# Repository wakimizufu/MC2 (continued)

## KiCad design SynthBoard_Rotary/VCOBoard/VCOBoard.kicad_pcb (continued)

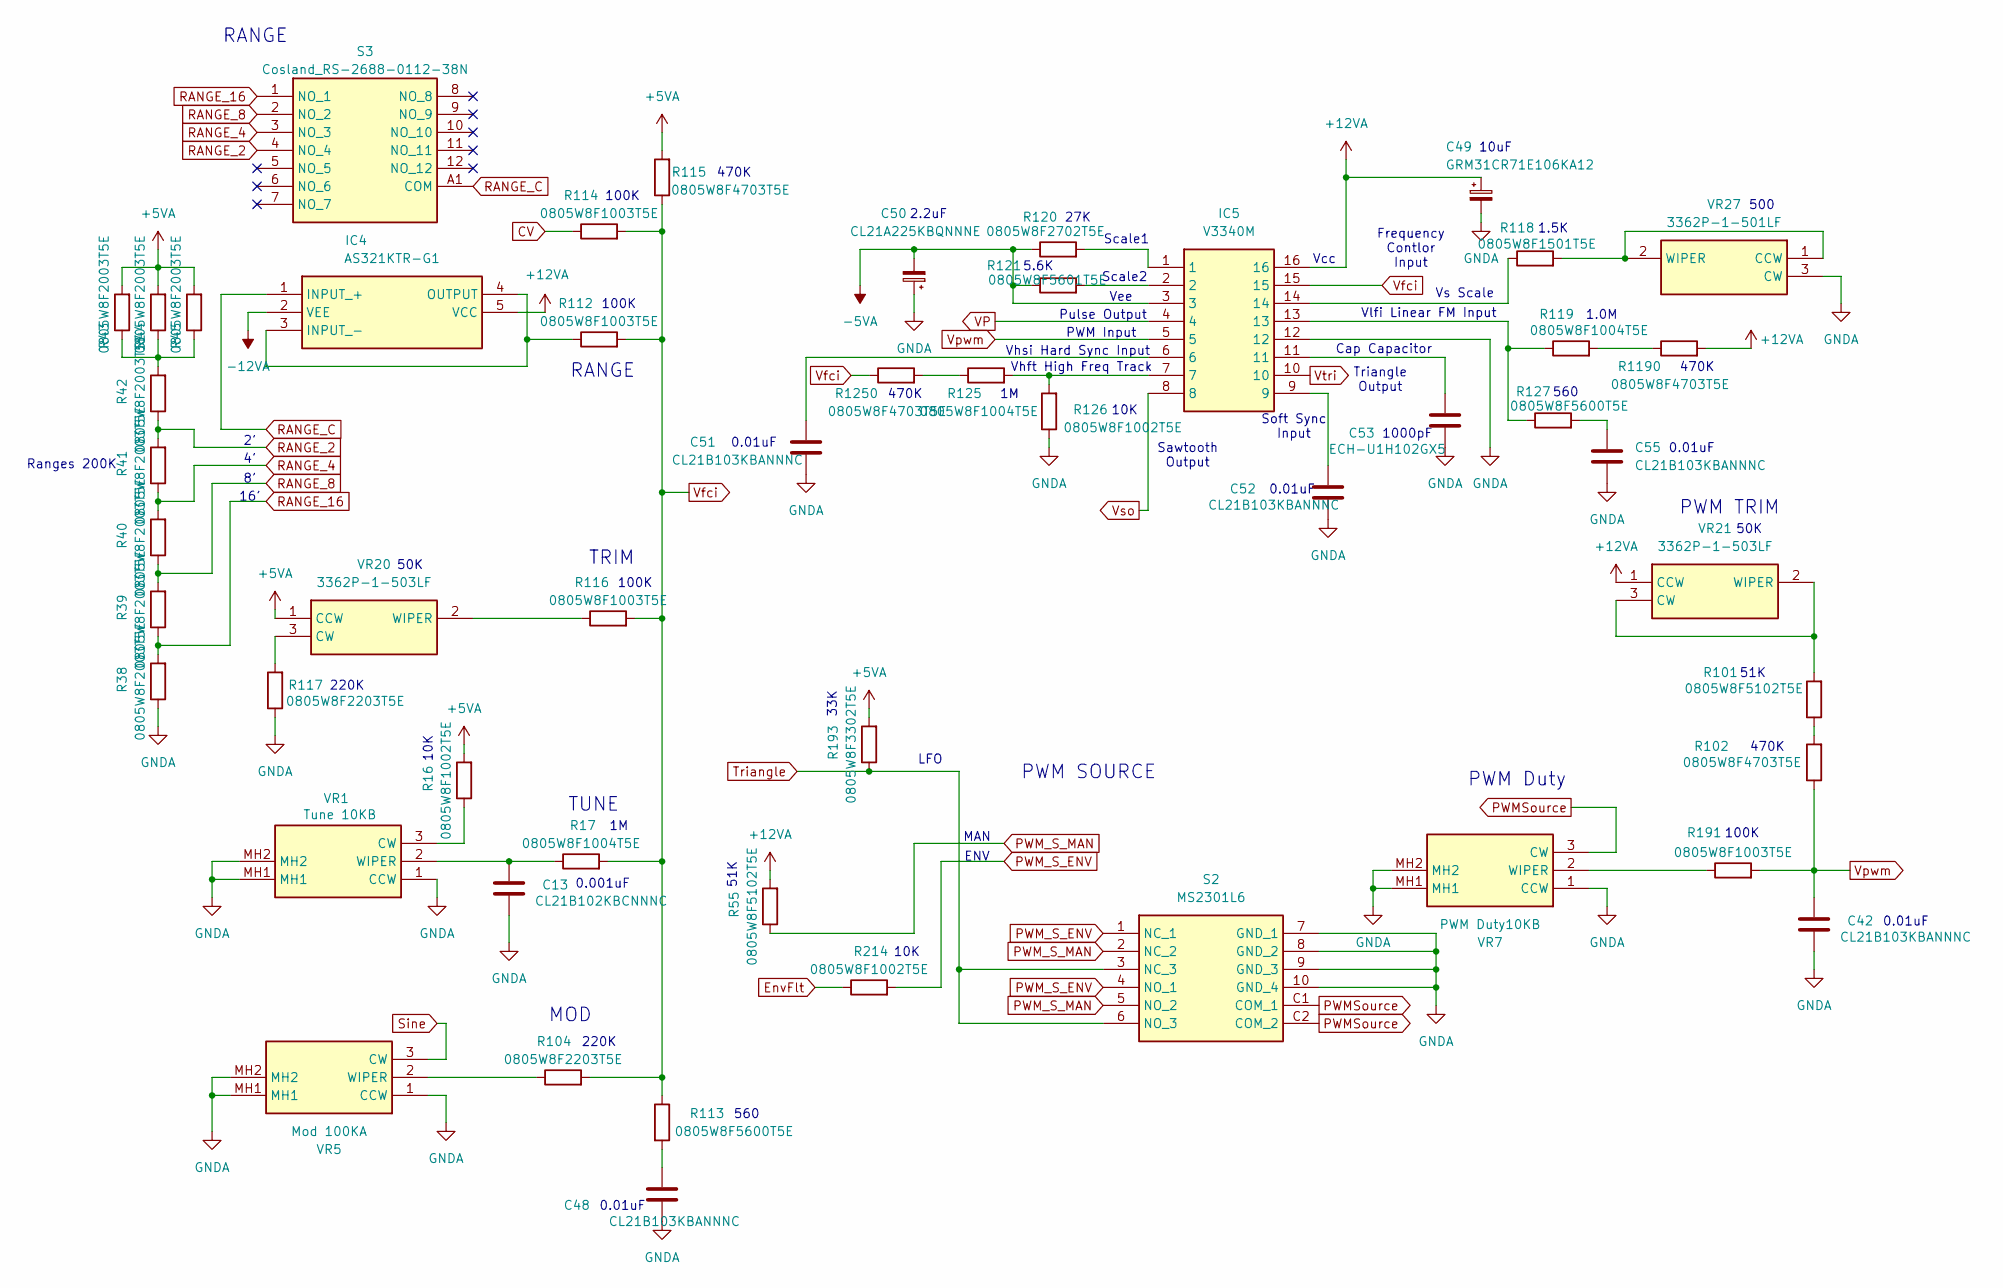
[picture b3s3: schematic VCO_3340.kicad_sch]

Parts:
C13: CL21B102KBCNNNC; C_0805_2012Metric_Pad1.18x1.45mm_HandSolder
C42, C48, C51, C52, C55: CL21B103KBANNNC; C_0805_2012Metric_Pad1.18x1.45mm_HandSolder
C49: GRM31CR71E106KA12; C_1206_3216Metric_Pad1.33x1.80mm_HandSolder
C50: CL21A225KBQNNNE; C_0805_2012Metric_Pad1.18x1.45mm_HandSolder
C53: ECH-U1H102GX5; C_0805_2012Metric_Pad1.18x1.45mm_HandSolder
IC4: AS321KTR-G1; SOT95P282X145-5N; Manufacturer_Part_Number AS321KTR-E1; Mouser Part Number 621-AS321KTR-E1
IC5: V3340M; SOP-16_3.9x9.9mm_P1.27mm; Manufacturer_Part_Number V3340M
R16, R126, R214: 0805W8F1002T5E; R_0805_2012Metric_Pad1.20x1.40mm_HandSolder
R17, R119, R125: 0805W8F1004T5E; R_0805_2012Metric_Pad1.20x1.40mm_HandSolder
R38, R39, R40, R41, R42, R43, R44, R45: 0805W8F2003T5E; R_0805_2012Metric_Pad1.20x1.40mm_HandSolder
R55, R101: 0805W8F5102T5E; R_0805_2012Metric_Pad1.20x1.40mm_HandSolder
R102, R115, R1190, R1250: 0805W8F4703T5E; R_0805_2012Metric_Pad1.20x1.40mm_HandSolder
R104, R117: 0805W8F2203T5E; R_0805_2012Metric_Pad1.20x1.40mm_HandSolder
R112, R114, R116, R191: 0805W8F1003T5E; R_0805_2012Metric_Pad1.20x1.40mm_HandSolder
R113, R127: 0805W8F5600T5E; R_0805_2012Metric_Pad1.20x1.40mm_HandSolder
R118: 0805W8F1501T5E; R_0805_2012Metric_Pad1.20x1.40mm_HandSolder
R120: 0805W8F2702T5E; R_0805_2012Metric_Pad1.20x1.40mm_HandSolder
R121: 0805W8F5601T5E; R_0805_2012Metric_Pad1.20x1.40mm_HandSolder
R193: 0805W8F3302T5E; R_0805_2012Metric_Pad1.20x1.40mm_HandSolder
S2: MS2301L6; Manufacturer_Part_Number MS2301L6
S3: Cosland_RS-2688-0112-38N; Manufacturer_Part_Number CK1054; Mouser Part Number 10WA344
VR1: Tune 10KB; RK09D117000B; Manufacturer_Part_Number RK09D117000B; Mouser Part Number 688-RK09D117000B
VR5: Mod 100KA; RK09D117000B; Manufacturer_Part_Number RK09D117000B; Mouser Part Number 688-RK09D117000B
VR7: PWM Duty10KB; RK09D117000B; Manufacturer_Part_Number RK09D117000B; Mouser Part Number 688-RK09D117000B
VR20, VR21: 3362P-1-503LF; 3362P_1; Manufacturer_Part_Number 3362P-1-103LF; Mouser Part Number 652-3362P-1-103LF
VR27: 3362P-1-501LF; 3362P_1; Manufacturer_Part_Number 3362P-1-103LF; Mouser Part Number 652-3362P-1-103LF

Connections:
+5VA: R16.2, R43.2, R44.2, R45.2, R115.2, R193.2, VR20.1 (CCW); also elsewhere on the board
+12VA: C49.1, IC4.5 (VCC), IC5.16, R55.2, R1190.2, VR21.1 (CCW); also elsewhere on the board
-5VA: C50.2, IC5.3, R120.1, R121.1; also elsewhere on the board
-12VA: IC4.2 (VEE); also elsewhere on the board
CV: R114.1; also elsewhere on the board
EnvFlt: R214.1; also elsewhere on the board
GNDA: C13.1, C42.1, C48.1, C49.2, C50.1, C51.1, C52.1, C53.1, C55.1, IC5.12, R38.1, R117.1, R126.1, S2.7 (GND_1), S2.8 (GND_2), S2.9 (GND_3), S2.10 (GND_4), VR1.1 (CCW), VR1.MH1, VR1.MH2, VR5.1 (CCW), VR5.MH1, VR5.MH2, VR7.1 (CCW), VR7.MH1, VR7.MH2, VR27.3 (CW); also elsewhere on the board
unnamed: C48.2, R113.2
unnamed: C51.2, IC5.6
unnamed: C52.2, IC5.9
unnamed: C53.2, IC5.11
unnamed: C55.2, R127.2
unnamed: IC4.3 (INPUT_-), IC4.4 (OUTPUT), R112.1
unnamed: IC5.1, R120.2
unnamed: IC5.2, R121.2
unnamed: IC5.7, R125.2, R126.2
unnamed: IC5.13, R119.1, R127.1
unnamed: IC5.14, R118.1
unnamed: R42.2, R43.1, R44.1, R45.1
unnamed: R101.1, R102.2
unnamed: R119.2, R1190.1
unnamed: R125.1, R1250.2
unnamed: R16.1, VR1.3 (CW)
unnamed: C13.2, R17.1, VR1.2 (WIPER)
unnamed: R104.1, VR5.2 (WIPER)
unnamed: R191.1, VR7.2 (WIPER)
unnamed: R117.2, VR20.3 (CW)
unnamed: R116.1, VR20.2 (WIPER)
unnamed: R101.2, VR21.2 (WIPER), VR21.3 (CW)
unnamed: R118.2, VR27.1 (CCW), VR27.2 (WIPER)
PWMSource: S2.C1 (COM_1), S2.C2 (COM_2), VR7.3 (CW)
PWM_S_ENV: R214.2, S2.1 (NC_1), S2.4 (NO_1)
PWM_S_MAN: R55.1, S2.2 (NC_2), S2.5 (NO_2)
RANGE_2: R41.2, R42.1, S3.4 (NO_4)
RANGE_4: R40.2, R41.1, S3.3 (NO_3)
RANGE_8: R39.2, R40.1, S3.2 (NO_2)
RANGE_16: R38.2, R39.1, S3.1 (NO_1)
RANGE_C: IC4.1 (INPUT_+), S3.A1 (COM)
Sine: VR5.3 (CW); also elsewhere on the board
Triangle: R193.1, S2.3 (NC_3), S2.6 (NO_3); also elsewhere on the board
VP: IC5.4; also elsewhere on the board
Vfci: IC5.15, R17.2, R104.2, R112.2, R113.1, R114.2, R115.1, R116.2, R1250.1
Vpwm: C42.2, IC5.5, R102.1, R191.2
Vso: IC5.8; also elsewhere on the board
Vtri: IC5.10; also elsewhere on the board

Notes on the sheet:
LFO
Scale2
Vcc
TRIM
0.01uF
560
Frequency Contlor Input
220K
10K
33K
RANGE
Pulse Output
10uF
27K
100K
PWM SOURCE
500
Vhsi Hard Sync Input
470K
Triangle Output
0.001uF
TUNE
PWM Input
51K
PWM Duty
1.5K
Sawtooth Output
PWM TRIM
1000pF
Vlfi Linear FM Input
MAN
16'
Vee
Soft Sync Input
Scale1
Ranges 200K
2.2uF
Vs Scale
ENV
50K

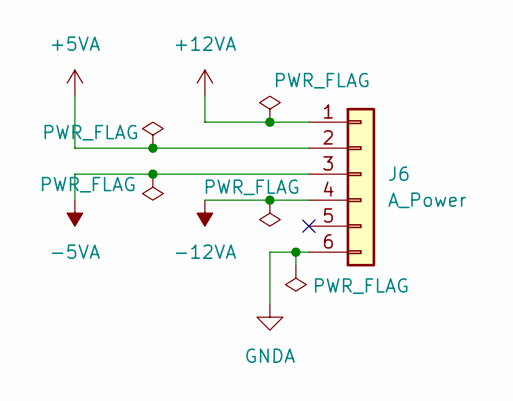
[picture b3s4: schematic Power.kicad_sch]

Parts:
J6: A_Power; PinHeader_1x06_P2.54mm_Vertical

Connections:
+5VA: J6.2; also elsewhere on the board
+12VA: J6.1; also elsewhere on the board
-5VA: J6.3; also elsewhere on the board
-12VA: J6.4; also elsewhere on the board
GNDA: J6.6; also elsewhere on the board

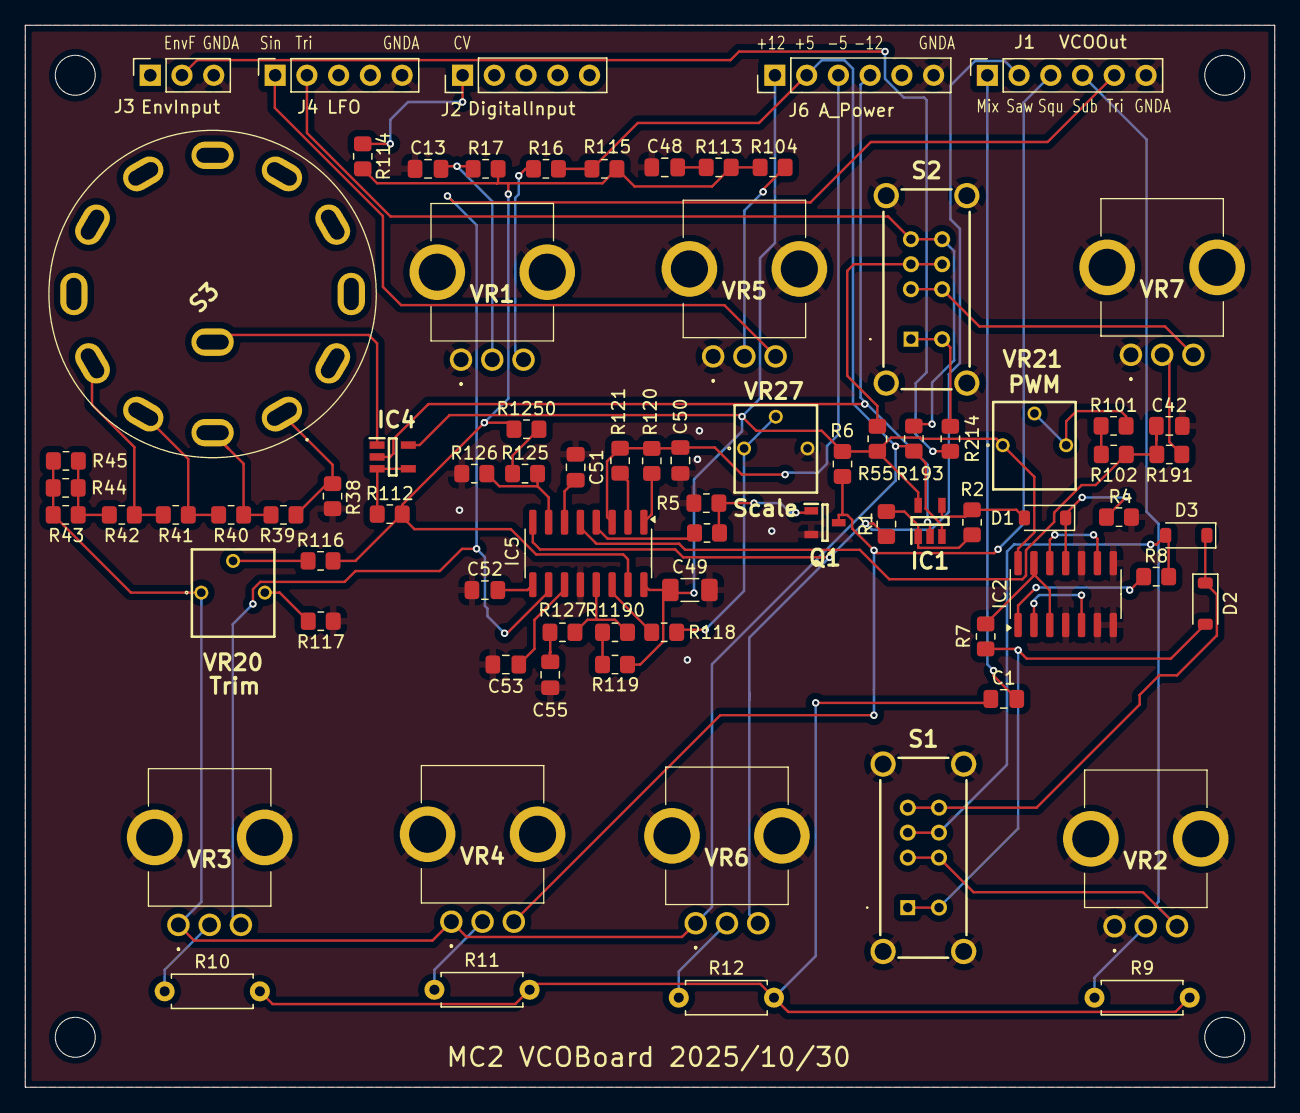
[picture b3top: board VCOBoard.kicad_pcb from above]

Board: 2 copper layers, 100.0 x 85.0 mm, 80 parts (0 on the bottom side), 64 nets.

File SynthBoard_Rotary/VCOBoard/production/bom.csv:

Designator,Footprint,Quantity,Value,LCSC Part #
C1,0805,1,CL21A106KAYNNNE,
C13,0805,1,CL21B102KBCNNNC,
"C42, C48, C51, C52, C55",0805,5,CL21B103KBANNNC,
C49,1206,1,C3216X5R1E476MTJ00E,
C50,0805,1,CL21A225KBQNNNE,
C53,0805,1,ECH-U1H102GX5,
"D1, D2, D3",D_SOD-123,3,1N4148W,
"IC1, IC4",SOT95P282X145-5N,2,AS321KTR-G1,
IC2,SOIC-14_3.9x8.7mm_P1.27mm,1,"HEF4013BT,653",
IC5,SOP-16_3.9x9.9mm_P1.27mm,1,V3340M,
J1,PinSocket_1x06_P2.54mm_Vertical,1,VCOOut,
J2,PinHeader_1x05_P2.54mm_Vertical,1,DigitalInput,
J3,PinSocket_1x03_P2.54mm_Vertical,1,EnvInput,
J4,PinSocket_1x05_P2.54mm_Vertical,1,LFO,
J6,PinHeader_1x06_P2.54mm_Vertical,1,A_Power,
Q1,SOT95P240X115-3N,1,SS8050(RANGE:200-350),
"R1, R193",0805,2,0805W8F3302T5E,
R10,R_Axial_DIN0207_L6.3mm_D2.5mm_P7.62mm_Horizontal,1,390K,
"R101, R55",0805,2,0805W8F5102T5E,
"R102, R115, R1190, R1250, R2",0805,5,0805W8F4703T5E,
"R104, R117",0805,2,0805W8F2203T5E,
"R11, R12",R_Axial_DIN0207_L6.3mm_D2.5mm_P7.62mm_Horizontal,2,470K,
"R112, R114, R116, R191",0805,4,0805W8F1003T5E,
"R113, R127",0805,2,0805W8F5600T5E,
R118,0805,1,0805W8F1501T5E,
"R119, R125, R17",0805,3,0805W8F1004T5E,
R120,0805,1,0805W8F2702T5E,
R121,0805,1,0805W8F5601T5E,
"R126, R16, R214, R3",0805,4,0805W8F1002T5E,
"R38, R39, R40, R41, R42, R43, R44, R45",0805,8,0805W8F2003T5E,
"R4, R7, R8",0805,3,0805W8F4702T5E,
R5,0805,1,0805W8F1001T5E,
R6,0805,1,0805W8F6802T5E,
R9,R_Axial_DIN0207_L6.3mm_D2.5mm_P7.62mm_Horizontal,1,1M,
"S1, S2",MS2301L6,2,MS2301L6,
S3,Cosland_RS-2688-0112-38N,1,Cosland_RS-2688-0112-38N,
VR1,RK09D117000B,1,Tune 10KB,
VR2,RK09D117000B,1,SubSquare 10KB,
"VR20, VR21",3362P_1,2,3362P-1-503LF,
VR27,3362P_1,1,3362P-1-501LF,
VR3,RK09D117000B,1,Triangle 100KB,
VR4,RK09D117000B,1,Square 10KB,
VR5,RK09D117000B,1,Mod 100KA,
VR6,RK09D117000B,1,Saw 100KB,
VR7,RK09D117000B,1,PWM Duty10KB,

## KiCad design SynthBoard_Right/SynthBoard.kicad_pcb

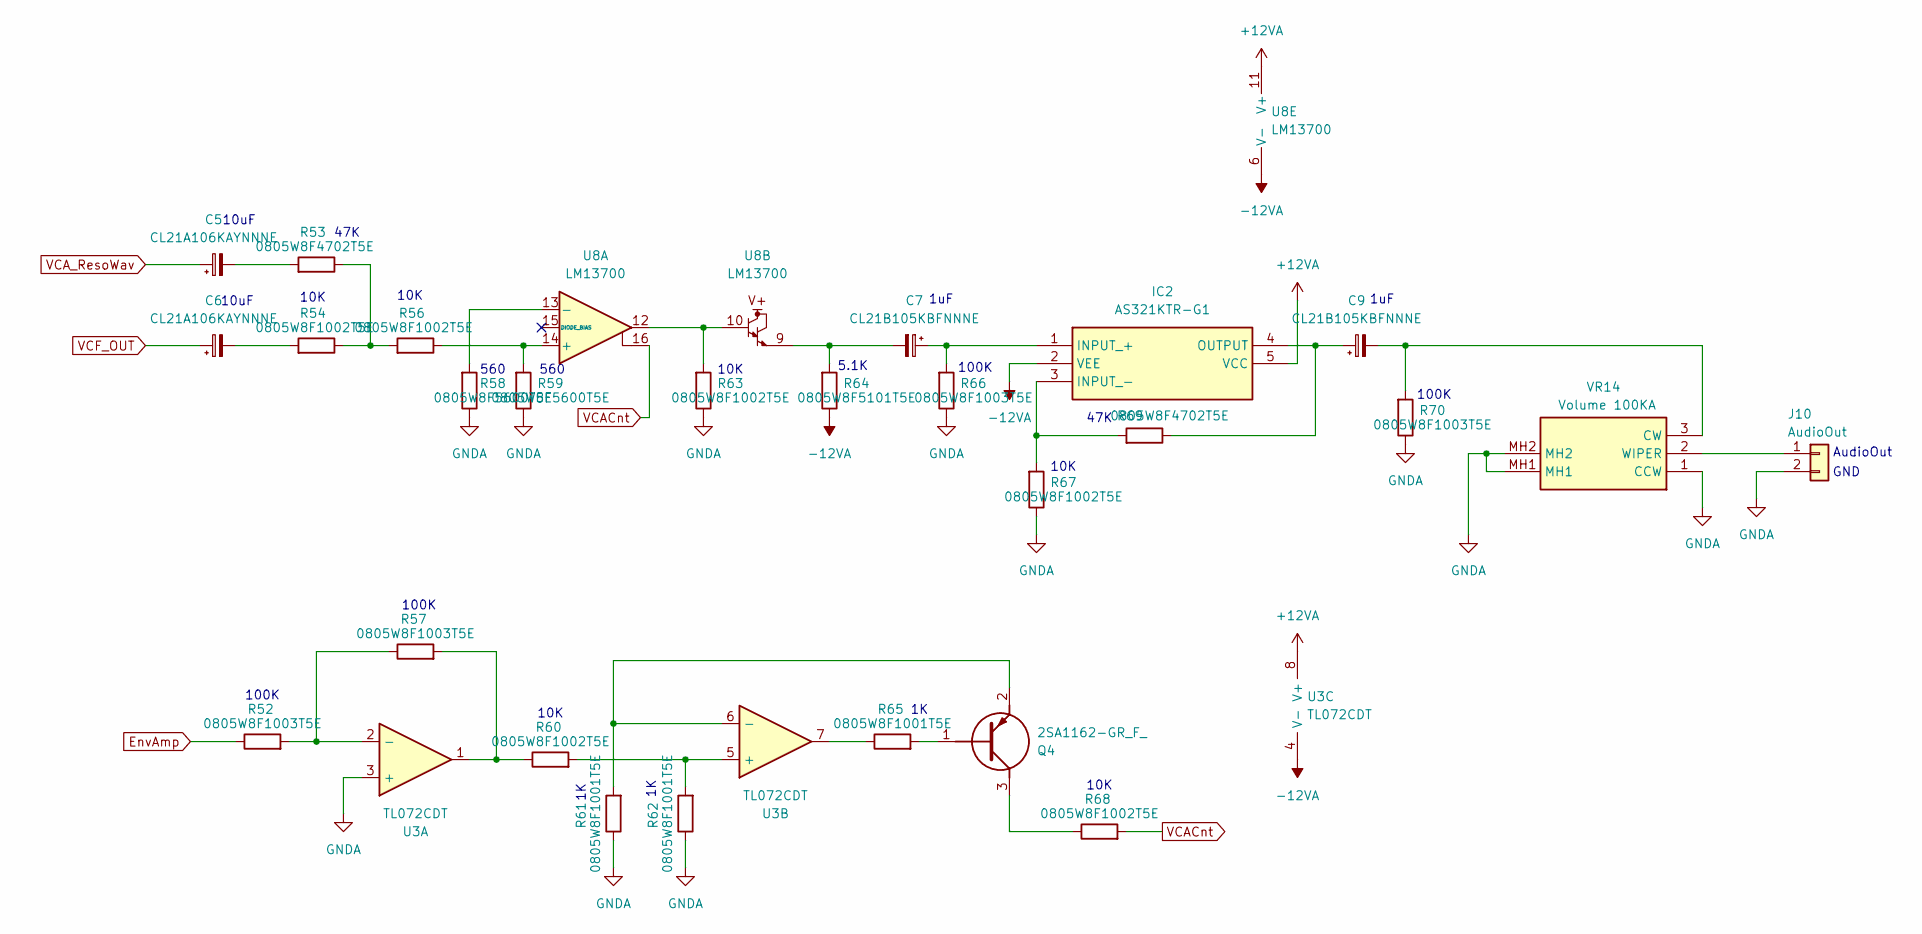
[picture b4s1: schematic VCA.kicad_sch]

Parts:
C5, C6: CL21A106KAYNNNE; C_0805_2012Metric_Pad1.18x1.45mm_HandSolder
C7, C9: CL21B105KBFNNNE; C_0805_2012Metric_Pad1.18x1.45mm_HandSolder
IC2: AS321KTR-G1; SOT95P282X145-5N; Manufacturer_Part_Number AS321KTR-E1; Mouser Part Number 621-AS321KTR-E1
J10: AudioOut; PinHeader_1x02_P2.54mm_Vertical
Q4: 2SA1162-GR_F_; 1SS294LFT; Manufacturer_Part_Number 2SA1162-GR(F)
R52, R57, R66, R70: 0805W8F1003T5E; R_0805_2012Metric_Pad1.20x1.40mm_HandSolder
R53, R69: 0805W8F4702T5E; R_0805_2012Metric_Pad1.20x1.40mm_HandSolder
R54, R56, R60, R63, R67, R68: 0805W8F1002T5E; R_0805_2012Metric_Pad1.20x1.40mm_HandSolder
R58, R59: 0805W8F5600T5E; R_0805_2012Metric_Pad1.20x1.40mm_HandSolder
R61, R62, R65: 0805W8F1001T5E; R_0805_2012Metric_Pad1.20x1.40mm_HandSolder
R64: 0805W8F5101T5E; R_0805_2012Metric_Pad1.20x1.40mm_HandSolder
U3: TL072CDT; SOIC-8_3.9x4.9mm_P1.27mm
U8: LM13700; SOIC-16_3.9x9.9mm_P1.27mm
VR14: Volume 100KA; RK09D117000B; Manufacturer_Part_Number RK09D117000B; Mouser Part Number 688-RK09D117000B

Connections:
+12VA: IC2.5 (VCC), U3.8 (V+), U8.11 (V+); also elsewhere on the board
-12VA: IC2.2 (VEE), R64.1, U3.4 (V-), U8.6 (V-); also elsewhere on the board
EnvAmp: R52.1; also elsewhere on the board
GNDA: J10.2, R58.1, R59.1, R61.1, R62.1, R63.1, R66.1, R67.1, R70.1, U3.3 (+), VR14.1 (CCW), VR14.MH1, VR14.MH2; also elsewhere on the board
unnamed: C5.2, R53.2
unnamed: C6.2, R54.2
unnamed: C7.2, R64.2, U8.9
unnamed: C7.1, IC2.1 (INPUT_+), R66.2
unnamed: IC2.3 (INPUT_-), R67.2, R69.2
unnamed: C9.1, IC2.4 (OUTPUT), R69.1
unnamed: J10.1, VR14.2 (WIPER)
unnamed: Q4.1 (B), R65.2
unnamed: Q4.3 (C), R68.1
unnamed: Q4.2 (E), R61.2, U3.6 (-)
unnamed: R53.1, R54.1, R56.2
unnamed: R57.2, R60.1, U3.1
unnamed: R63.2, U8.10, U8.12
unnamed: R65.1, U3.7
unnamed: R52.2, R57.1, U3.2 (-)
unnamed: R60.2, R62.2, U3.5 (+)
unnamed: R56.1, R59.2, U8.14 (+)
unnamed: R58.2, U8.13 (-)
unnamed: C9.2, R70.2, VR14.3 (CW)
VCACnt: R68.2, U8.16
VCA_ResoWav: C5.1; also elsewhere on the board
VCF_OUT: C6.1; also elsewhere on the board

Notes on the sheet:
10K
100K
47K
1uF
10uF
5.1K
560
GND
AudioOut

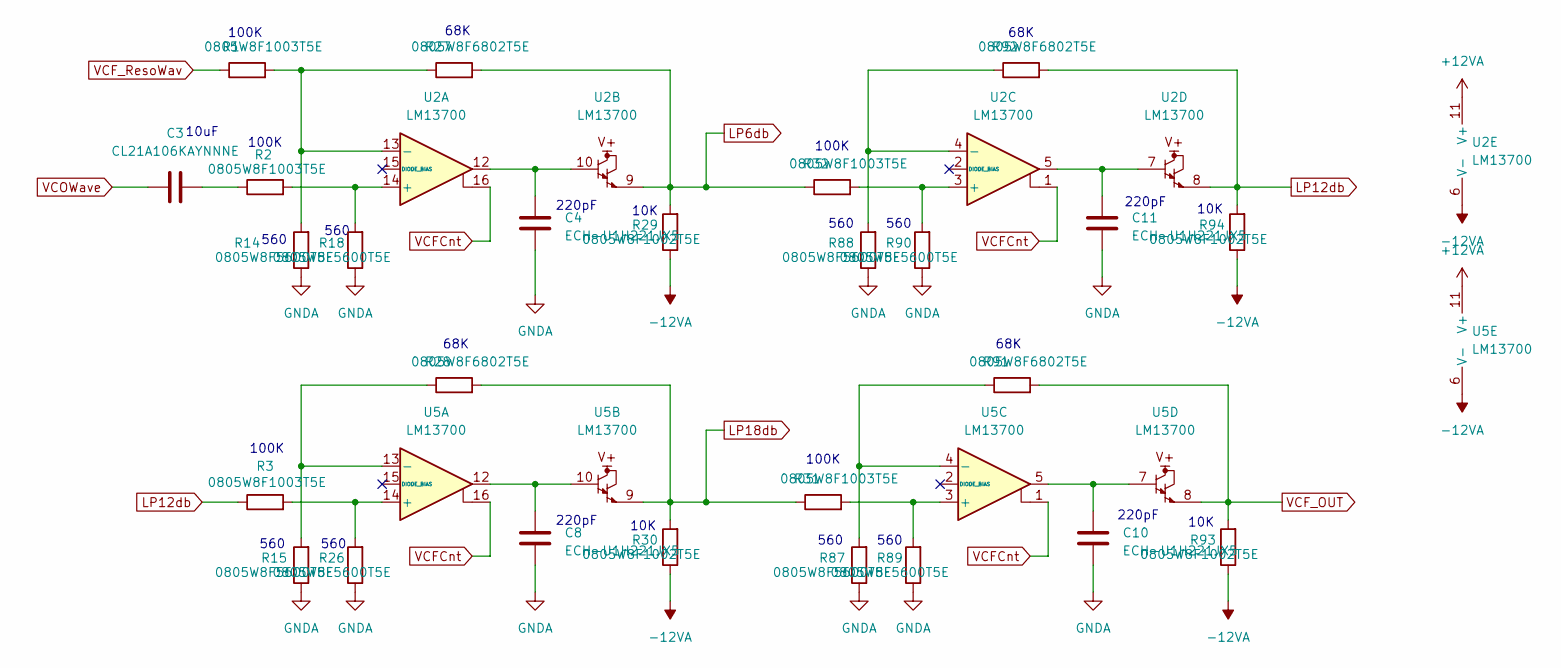
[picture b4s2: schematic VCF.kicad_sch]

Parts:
C3: CL21A106KAYNNNE; C_0805_2012Metric_Pad1.18x1.45mm_HandSolder
C4, C8, C10, C11: ECH-U1H221JX5; C_0805_2012Metric_Pad1.18x1.45mm_HandSolder
R1, R2, R3, R31, R32: 0805W8F1003T5E; R_0805_2012Metric_Pad1.20x1.40mm_HandSolder
R14, R15, R18, R26, R87, R88, R89, R90: 0805W8F5600T5E; R_0805_2012Metric_Pad1.20x1.40mm_HandSolder
R27, R28, R91, R92: 0805W8F6802T5E; R_0805_2012Metric_Pad1.20x1.40mm_HandSolder
R29, R30, R93, R94: 0805W8F1002T5E; R_0805_2012Metric_Pad1.20x1.40mm_HandSolder
U2, U5: LM13700; SOIC-16_3.9x9.9mm_P1.27mm

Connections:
+12VA: U2.11 (V+), U5.11 (V+); also elsewhere on the board
-12VA: R29.1, R30.1, R93.1, R94.1, U2.6 (V-), U5.6 (V-); also elsewhere on the board
GNDA: C4.2, C8.2, C10.2, C11.2, R14.1, R15.1, R18.1, R26.1, R87.1, R88.1, R89.1, R90.1; also elsewhere on the board
LP6db: R27.2, R29.2, R32.1, U2.9
LP12db: R3.1, R92.2, R94.2, U2.8
LP18db: R28.2, R30.2, R31.1, U5.9
unnamed: C3.2, R2.1
unnamed: C4.1, U2.10, U2.12
unnamed: C8.1, U5.10, U5.12
unnamed: C10.1, U5.5, U5.7
unnamed: C11.1, U2.5, U2.7
unnamed: R2.2, R18.2, U2.14 (+)
unnamed: R1.2, R14.2, R27.1, U2.13 (-)
unnamed: R32.2, R90.2, U2.3 (+)
unnamed: R88.2, R92.1, U2.4 (-)
unnamed: R3.2, R26.2, U5.14 (+)
unnamed: R15.2, R28.1, U5.13 (-)
unnamed: R31.2, R89.2, U5.3 (+)
unnamed: R87.2, R91.1, U5.4 (-)
VCFCnt: U2.1, U2.16, U5.1, U5.16; also elsewhere on the board
VCF_OUT: R91.2, R93.2, U5.8; also elsewhere on the board
VCF_ResoWav: R1.1; also elsewhere on the board
VCOWave: C3.1; also elsewhere on the board

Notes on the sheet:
560
10K
220pF
68K
100K
10uF

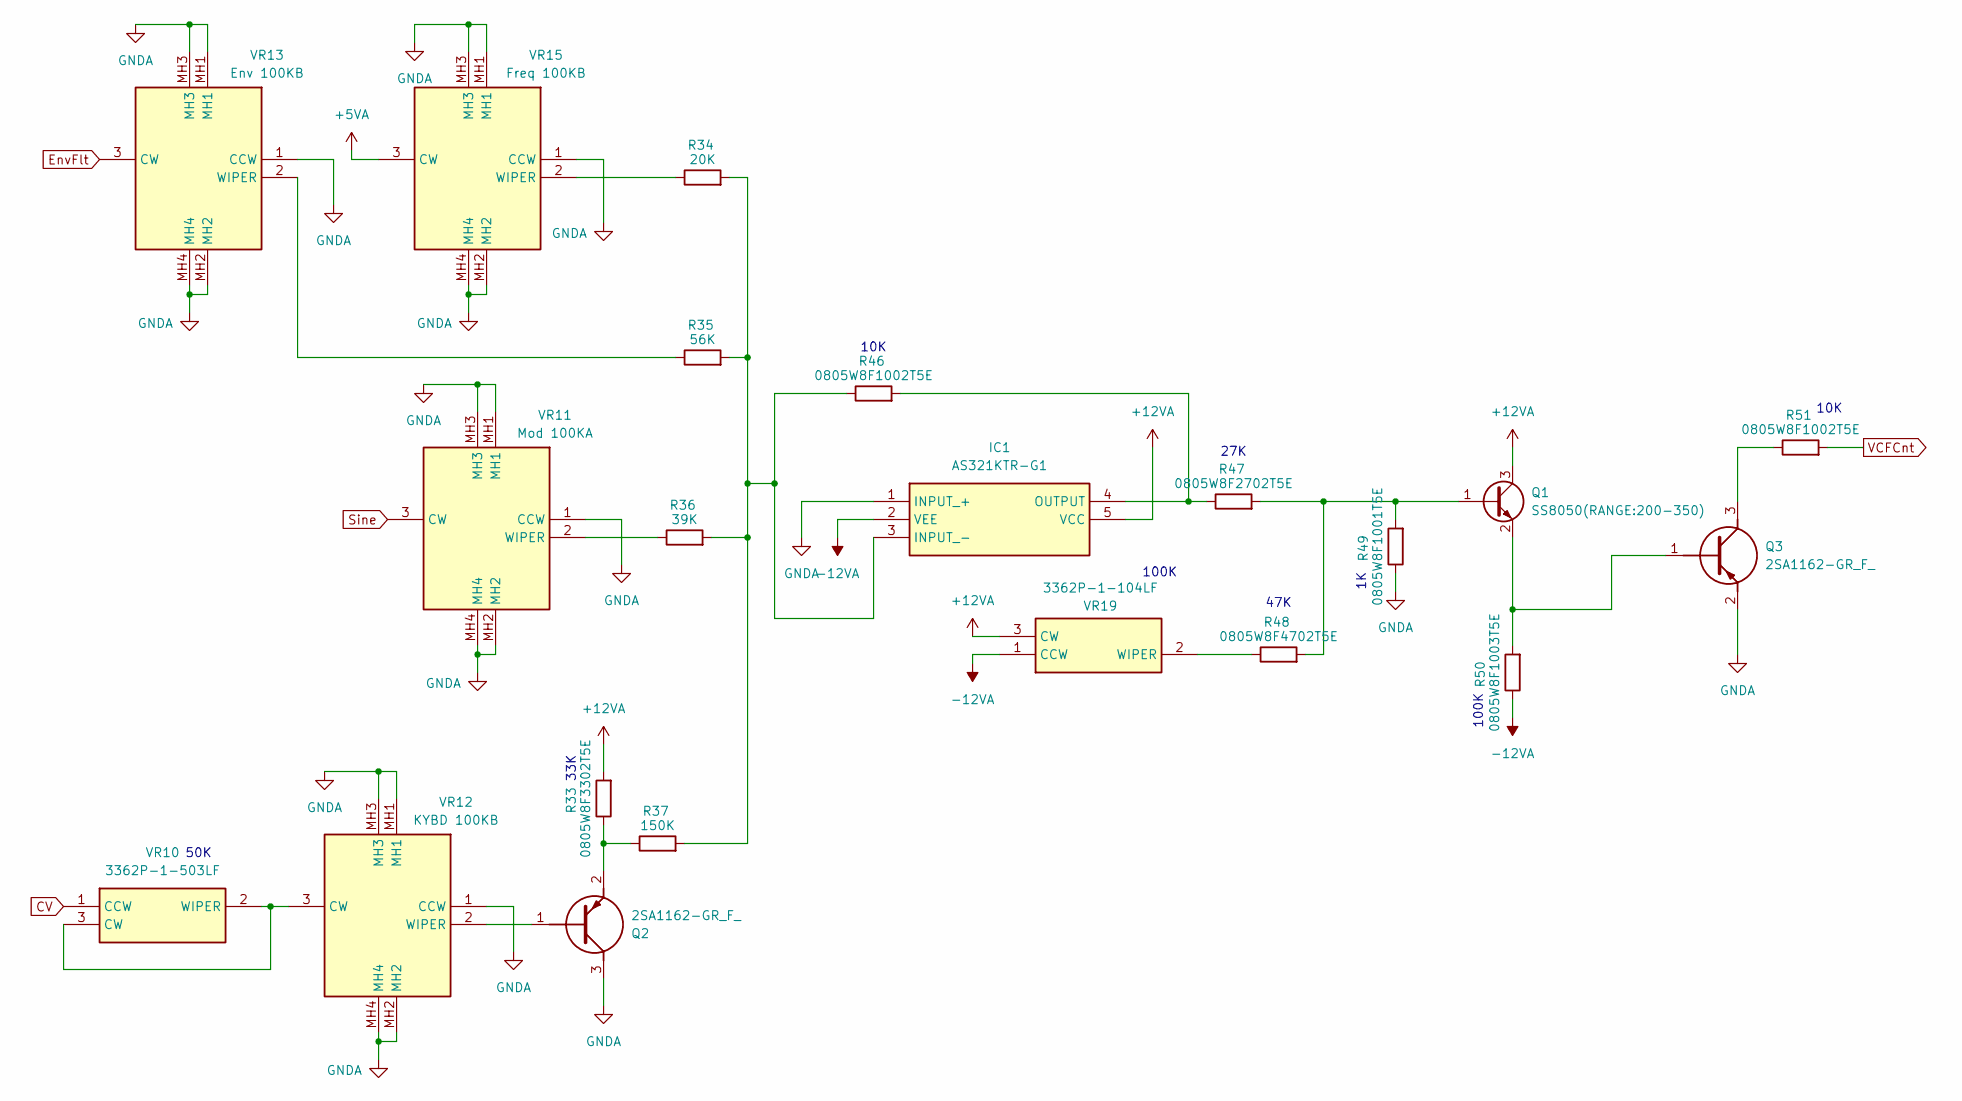
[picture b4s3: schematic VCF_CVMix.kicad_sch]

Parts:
IC1: AS321KTR-G1; SOT95P282X145-5N; Manufacturer_Part_Number AS321KTR-E1; Mouser Part Number 621-AS321KTR-E1
Q1: SS8050(RANGE:200-350); SOT-23
Q2, Q3: 2SA1162-GR_F_; 1SS294LFT; Manufacturer_Part_Number 2SA1162-GR(F)
R33: 0805W8F3302T5E; R_0805_2012Metric_Pad1.20x1.40mm_HandSolder
R34: 20K; R_Axial_DIN0204_L3.6mm_D1.6mm_P7.62mm_Horizontal
R35: 56K; R_Axial_DIN0204_L3.6mm_D1.6mm_P7.62mm_Horizontal
R36: 39K; R_Axial_DIN0204_L3.6mm_D1.6mm_P7.62mm_Horizontal
R37: 150K; R_Axial_DIN0204_L3.6mm_D1.6mm_P7.62mm_Horizontal
R46, R51: 0805W8F1002T5E; R_0805_2012Metric_Pad1.20x1.40mm_HandSolder
R47: 0805W8F2702T5E; R_0805_2012Metric_Pad1.20x1.40mm_HandSolder
R48: 0805W8F4702T5E; R_0805_2012Metric_Pad1.20x1.40mm_HandSolder
R49: 0805W8F1001T5E; R_0805_2012Metric_Pad1.20x1.40mm_HandSolder
R50: 0805W8F1003T5E; R_0805_2012Metric_Pad1.20x1.40mm_HandSolder
VR10: 3362P-1-503LF; 3362P_1; Manufacturer_Part_Number 3362P-1-103LF; Mouser Part Number 652-3362P-1-103LF
VR11: Mod 100KA; PTA20432010CIB104; Manufacturer_Part_Number PTA2043-2010CIB104; Mouser Part Number 652-PTA2432010CIB104
VR12: KYBD 100KB; PTA20432010CIB104; Manufacturer_Part_Number PTA2043-2010CIB104; Mouser Part Number 652-PTA2432010CIB104
VR13: Env 100KB; PTA20432010CIB104; Manufacturer_Part_Number PTA2043-2010CIB104; Mouser Part Number 652-PTA2432010CIB104
VR15: Freq 100KB; PTA20432010CIB104; Manufacturer_Part_Number PTA2043-2010CIB104; Mouser Part Number 652-PTA2432010CIB104
VR19: 3362P-1-104LF; 3362P_1; Manufacturer_Part_Number 3362P-1-103LF; Mouser Part Number 652-3362P-1-103LF

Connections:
+5VA: VR15.3 (CW); also elsewhere on the board
+12VA: IC1.5 (VCC), Q1.3 (C), R33.2, VR19.3 (CW); also elsewhere on the board
-12VA: IC1.2 (VEE), R50.1, VR19.1 (CCW); also elsewhere on the board
CV: VR10.1 (CCW); also elsewhere on the board
EnvFlt: VR13.3 (CW); also elsewhere on the board
GNDA: IC1.1 (INPUT_+), Q2.3 (C), Q3.2 (E), R49.1, VR11.1 (CCW), VR11.MH1, VR11.MH2, VR11.MH3, VR11.MH4, VR12.1 (CCW), VR12.MH1, VR12.MH2, VR12.MH3, VR12.MH4, VR13.1 (CCW), VR13.MH1, VR13.MH2, VR13.MH3, VR13.MH4, VR15.1 (CCW), VR15.MH1, VR15.MH2, VR15.MH3, VR15.MH4; also elsewhere on the board
unnamed: IC1.3 (INPUT_-), R34.2, R35.2, R36.2, R37.2, R46.1
unnamed: IC1.4 (OUTPUT), R46.2, R47.1
unnamed: Q1.1 (B), R47.2, R48.2, R49.2
unnamed: Q1.2 (E), Q3.1 (B), R50.2
unnamed: Q2.1 (B), VR12.2 (WIPER)
unnamed: Q2.2 (E), R33.1, R37.1
unnamed: Q3.3 (C), R51.1
unnamed: VR10.2 (WIPER), VR10.3 (CW), VR12.3 (CW)
unnamed: R36.1, VR11.2 (WIPER)
unnamed: R35.1, VR13.2 (WIPER)
unnamed: R34.1, VR15.2 (WIPER)
unnamed: R48.1, VR19.2 (WIPER)
Sine: VR11.3 (CW); also elsewhere on the board
VCFCnt: R51.2; also elsewhere on the board

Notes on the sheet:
100K
47K
10K
27K
50K
33K

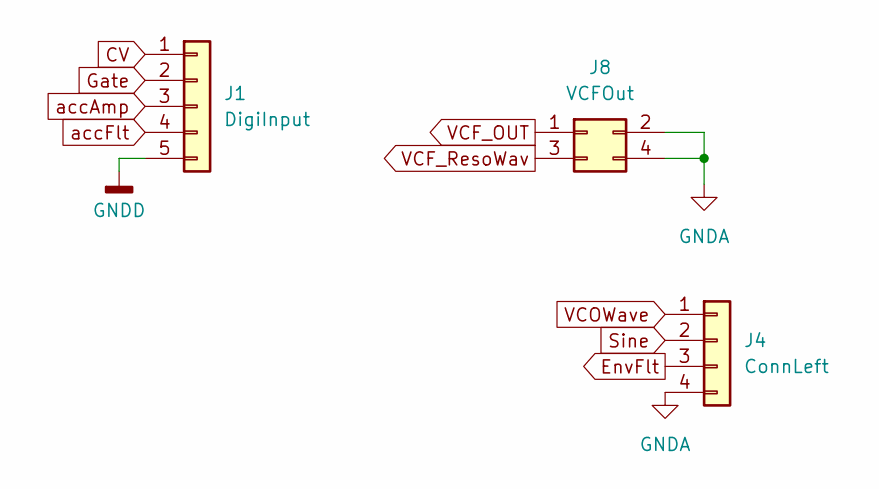
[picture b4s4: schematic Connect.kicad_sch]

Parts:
J1: DigiInput; PinSocket_1x05_P2.54mm_Vertical
J4: ConnLeft; PinSocket_1x04_P2.54mm_Vertical
J8: VCFOut; PinSocket_2x02_P2.54mm_Vertical

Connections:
CV: J1.1; also elsewhere on the board
EnvFlt: J4.3; also elsewhere on the board
GNDA: J4.4, J8.2, J8.4; also elsewhere on the board
GNDD: J1.5; also elsewhere on the board
Gate: J1.2; also elsewhere on the board
Sine: J4.2; also elsewhere on the board
VCF_OUT: J8.1; also elsewhere on the board
VCF_ResoWav: J8.3; also elsewhere on the board
VCOWave: J4.1; also elsewhere on the board
accAmp: J1.3; also elsewhere on the board
accFlt: J1.4; also elsewhere on the board

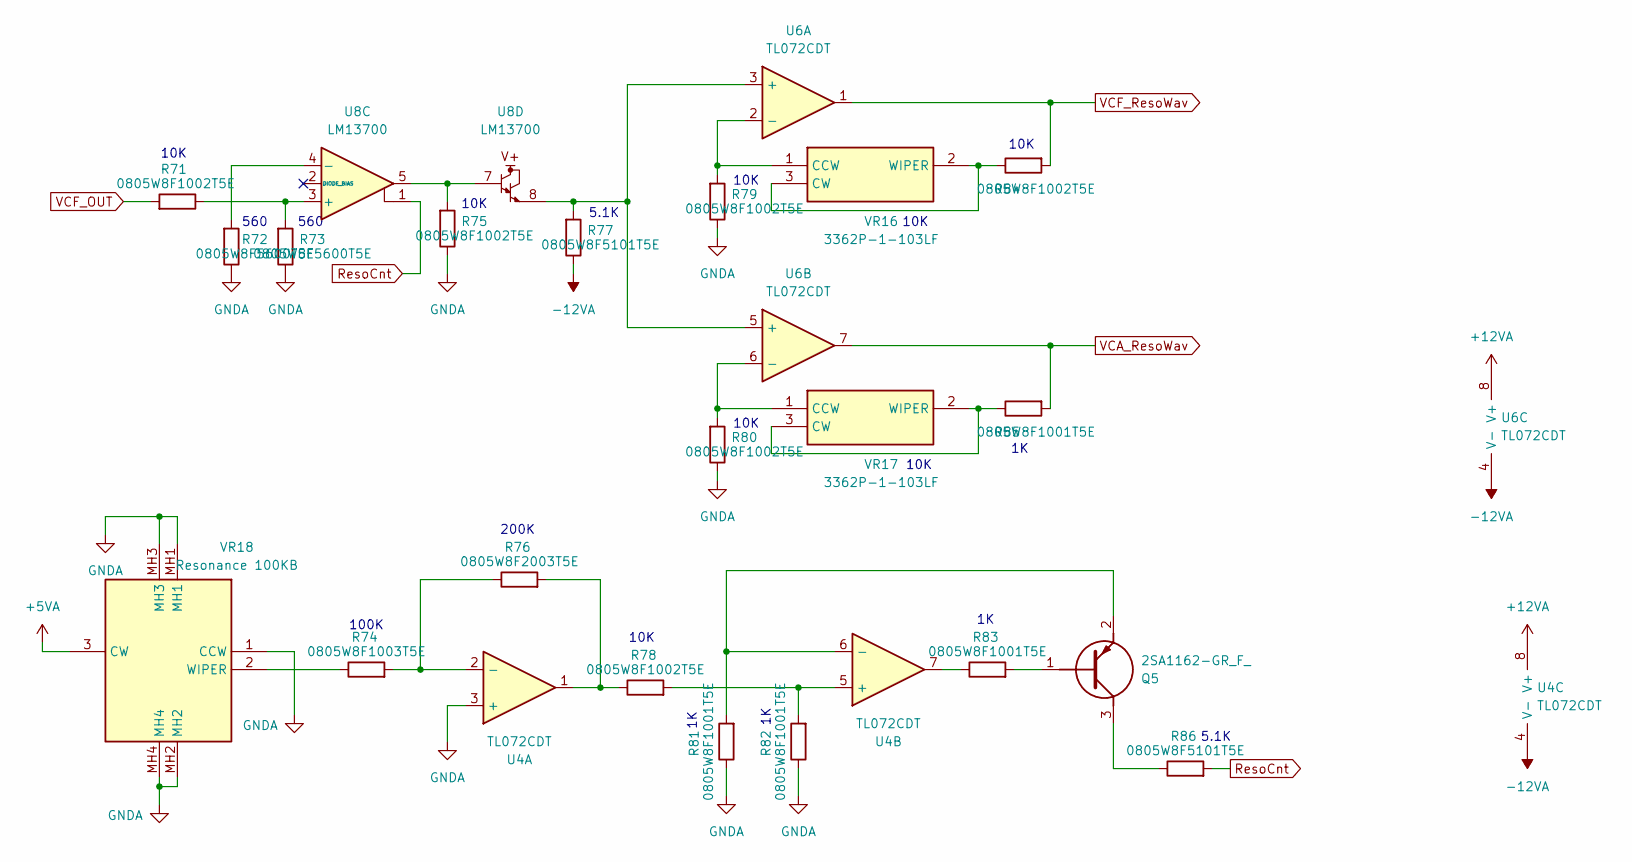
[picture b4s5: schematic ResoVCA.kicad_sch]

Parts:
Q5: 2SA1162-GR_F_; 1SS294LFT; Manufacturer_Part_Number 2SA1162-GR(F)
R71, R75, R78, R79, R80, R84: 0805W8F1002T5E; R_0805_2012Metric_Pad1.20x1.40mm_HandSolder
R72, R73: 0805W8F5600T5E; R_0805_2012Metric_Pad1.20x1.40mm_HandSolder
R74: 0805W8F1003T5E; R_0805_2012Metric_Pad1.20x1.40mm_HandSolder
R76: 0805W8F2003T5E; R_0805_2012Metric_Pad1.20x1.40mm_HandSolder
R77, R86: 0805W8F5101T5E; R_0805_2012Metric_Pad1.20x1.40mm_HandSolder
R81, R82, R83, R85: 0805W8F1001T5E; R_0805_2012Metric_Pad1.20x1.40mm_HandSolder
U4, U6: TL072CDT; SOIC-8_3.9x4.9mm_P1.27mm
U8: LM13700; SOIC-16_3.9x9.9mm_P1.27mm
VR16, VR17: 3362P-1-103LF; 3362P_1; Manufacturer_Part_Number 3362P-1-103LF; Mouser Part Number 652-3362P-1-103LF
VR18: Resonance 100KB; PTA20432010CIB104; Manufacturer_Part_Number PTA2043-2010CIB104; Mouser Part Number 652-PTA2432010CIB104

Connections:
+5VA: VR18.3 (CW); also elsewhere on the board
+12VA: U4.8 (V+), U6.8 (V+); also elsewhere on the board
-12VA: R77.1, U4.4 (V-), U6.4 (V-); also elsewhere on the board
GNDA: R72.1, R73.1, R75.1, R79.1, R80.1, R81.1, R82.1, U4.3 (+), VR18.1 (CCW), VR18.MH1, VR18.MH2, VR18.MH3, VR18.MH4; also elsewhere on the board
unnamed: Q5.1 (B), R83.2
unnamed: Q5.3 (C), R86.1
unnamed: Q5.2 (E), R81.2, U4.6 (-)
unnamed: R75.2, U8.5, U8.7
unnamed: R76.2, R78.1, U4.1
unnamed: R83.1, U4.7
unnamed: R74.2, R76.1, U4.2 (-)
unnamed: R78.2, R82.2, U4.5 (+)
unnamed: R77.2, U6.3 (+), U6.5 (+), U8.8
unnamed: R79.2, U6.2 (-), VR16.1 (CCW)
unnamed: R80.2, U6.6 (-), VR17.1 (CCW)
unnamed: R71.1, R73.2, U8.3 (+)
unnamed: R72.2, U8.4 (-)
unnamed: R84.1, VR16.2 (WIPER), VR16.3 (CW)
unnamed: R85.1, VR17.2 (WIPER), VR17.3 (CW)
unnamed: R74.1, VR18.2 (WIPER)
ResoCnt: R86.2, U8.1
VCA_ResoWav: R85.2, U6.7; also elsewhere on the board
VCF_OUT: R71.2; also elsewhere on the board
VCF_ResoWav: R84.2, U6.1; also elsewhere on the board

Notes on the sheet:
10K
560
100K
5.1K
200K

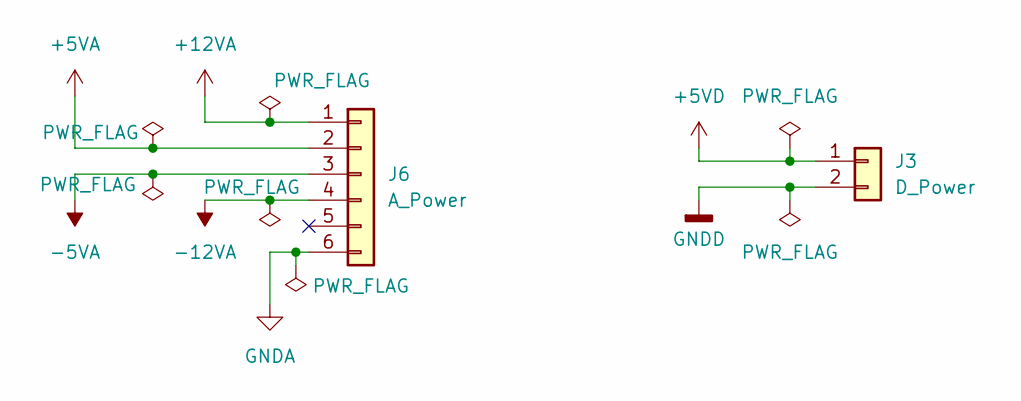
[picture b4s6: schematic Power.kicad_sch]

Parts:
J3: D_Power; PinSocket_1x02_P2.54mm_Vertical
J6: A_Power; PinHeader_1x06_P2.54mm_Vertical

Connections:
+5VA: J6.2; also elsewhere on the board
+5VD: J3.1; also elsewhere on the board
+12VA: J6.1; also elsewhere on the board
-5VA: J6.3
-12VA: J6.4; also elsewhere on the board
GNDA: J6.6; also elsewhere on the board
GNDD: J3.2; also elsewhere on the board
